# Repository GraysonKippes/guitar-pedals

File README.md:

# Guitar Pedals
A collection of custom guitar pedals designed and built by me.
## Fuzzy Mk. 1
[Main Article](fuzz_mk1/)

A simple fuzz pedal, this is my first guitar pedal.
It amplifies the input signal and limits the output signal, shaping it into a more blocky, thick waveform.
The circuit consists of an op-amp amplifier-limiter circuit, as well as a 2:1 analog mux and an electronic toggle latch for bypass functionality.
It runs on 9VDC, which is standard for guitar pedals.

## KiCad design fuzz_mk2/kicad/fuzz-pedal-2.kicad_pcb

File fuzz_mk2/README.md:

# Fuzzy Mk. 2
The Fuzzy Mk. 2 is an analog fuzz-style distortion pedal with two-band tone control.

## Circuit Overview
The effect path consists of two stages: the fuzz distortion, then the tone control.
The fuzz distortion is the main part of the circuit, and the tone control is an add-on inspired by the Big Muff Pi requested by my client.
I upcharged him (and every other buyer) for it.

### Fuzz Distortion
Fuzz distortion works by heavily amplifying a signal past the output range of the amplifier, resulting in a heavily clipped waveform that resembles a square wave.
Like the Mk. 1, I implement this clipping not with overdriving an amplifier, but with an op-amp limiter circuit.
This means I control the limit level in the signal feedback path, rather than by adjusting the voltage delivered to the op-amp's supply pins.
Op-amps often have assymetrical headroom under the positive rail and over the negative rail; i.e. output can get closer to the negative rail than to the positive rail.
This would result in an assymetrical clipping, which, while probably an interesting distortion effect, is not what I am going for.
(At any rate, I could implement assymetrical clipping in the signal feedback path if I wanted to.)

Also, controlling the limit level through the power rails would most likely amount to powering the op-amp through a voltage divider, and the op-amp itself would end up loading the voltage divider when it draws current, changing the divider ratio.
On top of that, using the power rails to control the signal in such a way would leak any ripple in the power supply into the signal, which is incredibly undesirable.

As a side note, I believe that one could implement "softer" distortions (such as overdrive) by increasing the resistances of the resistors in the limiter voltage divider, relative to the resistors in the amplifier voltage divider.
This would cause the limiter to "sag" and not clip the signal as hard.

### Tone Control
The tone control works by splitting the signal path into two paths: one that is fed into a low-pass filter, and one that is fed into a high-pass filter.
The two paths are then added back together.

More specifically, my tone control is essentially the Big Muff Pi (by Electro-Harmonix) tone control, with two crucial modifications.
1. The filters and the adder circuits were converted from one big passive network to three op-amp circuits, effectively buffering each stage.
2. The filters were designed to share the same cut-off frequency, rather than have two separate frequencies.

By converting the passive network into distinct active stages, they no longer sag each other down.
Also, by making the tone control stages active, I can further boost the signal if needed and buffer the output, not having a high impedance output.

The original Big Muff Pi pedal has a different cut-off frequency for each filter, with a lower cut-off for the low-pass filter and a higher cut-off for the high-pass filter.
When the two filtered paths are added back together, a gap is left behind in the frequency response.
This is the "mid-range scoop" for which this pedal is infamous; guitarists have agonized over how to compensate for this, when I simply restore that band of frequencies.

The adder stage of the tone control consists of nothing more than a potentiometer (which connects the outputs of the filters together) with the center tap buffered by an op-amp.
This allows the user to set a ratio with which the low-pass and high-pass lines are mixed.
For example, setting the pot wiper three-quarters along the way to the low-pass end means that the output will receive 75% low-pass and 25% high-pass.

My main goal with the tone control was to have it so that the frequency response would be totally flat when set to 50/50 mix; that is, the signal would sound the same, as though there was no tone control at all.
matching the cut-off frequencies of the filters ensures this, and this can be proven mathematically by adding the frequency responses of the two filters:

$$ \frac{1}{1 + sRC} + \frac{sRC}{1 + sRC} = \frac{1 + sRC}{1 + sRC} = 1 $$

This result is confirmed with an LTspice simulation of the tone control circuit.

## Component Selection

### Operational Amplifiers
In my opinion, the only components in this circuit worth discussing in depth are the op-amps; no need to discuss the resistors and capacitors.
I originally wanted to pick out nice op-amps from the Burr-Brown line, and I spent a lot of time sifting through the parts.
I settled on an OPA1641 for the buffer input and an OPA1679 for the signal processing.
However, by the time I got around to ordering the parts, the OPA1679 went out of stock.
(This has happened before too, with an STM32H7A3, which is why that project is on hiatus).
So I bought a TL074 instead, which is thankfully pin-compatible.

All the noiselessness of the newer op-amps is pretty much pointless anyways, given the fact that guitar pedal setups are riff with stray inductances and ground loops.
So for this reason (and a few others), I will probably just stick to the TL07x and NE5532 op-amps going forward.

I picked the OPA1641 because it is a JFET input and thus has much higher input impedance and can handle higher impedance sources.
According the Google, JFET inputs are supposed to have this rich, warm tone to them that guitarists like.
It's probably nonsense, but when in Rome, do as the Romans do.

I picked a quad op-amp package for the signal processing to fit it all into one neat package, but it ended up being more a hassle to route to be honest.
The main benefit I see of quad op-amps is that they seem to all or mostly use the same standard pin-out, whereas single- and dual- packages have different pin-outs.
I have read before that quad op-amps have all these issues, including increased crosstalk noise and higher power consumption; but to be honest, other than the more restricted routing, I doubt that these supposed issues are real, or if they are real, actually matter.
Again, the noise from patch cables and ground loop hums dominates whatever noise there is or isn't in the op-amps.

### Indicator LEDs
I selected a green LED for the power-on indicator and a blue LED for the effect-on indicator.
The consquence of this was that I needed two different current-limiting resistors to match their power levels.
For each LED, I calculate the resistance needed using Ohm's Law with the forward voltage and test current in the LED's datasheet:

$$ R_{LED} = \frac{V_{CC} - V_{F}}{I_{F}}$$

The calculated resistance value must be rounded to the nearest standard EIA value.

## Comparison to Fuzzy Mk. 1
In all honesty, the first fuzz pedal was completely overengineered with the analog mux and the 555 timer used as a bistable latch.
Getting rid of those massively simplified the circuit design and freed up room for other circuitry (namely the tone control).
At any rate, the 555-based toggle functionality was really buggy and just a nuisance overall.
Probably the biggest embarrassment in my opinion was using the 555 timer output to control a transistor switch that in turn controlled the mux, which was utterly pointless.

I still believe that an electronic switch (controlled by a mechanical switch) is superior to a purely mechanical switch for a few reasons.
1. Switch bouncing can be eliminated by placing a low-pass filter on the base/gate of the electronic switch.
2. The signal path does not have to be run all the way back to the footswitch (optimizing PCB trace length is pointless for noise, but it would make routing easier).
3. The switch could be controlled however I want, and I am not just limited to the mechanical switch functionality.
That being said, I would rather implement the electronic switching with discrete transistors than spend $6 on a single mux IC again, especially since switches are needed on both the input and output, doubling the cost.

Besides the core circuit design, I also introduced circuit protection to Fuzzy Mk. 2, which was not at all present in Mk. 1.
Fuzzy Mk. 2 includes reverse polarity protection and overvoltage protection on the power port, as well as ESD protection on both power port and audio jacks.
Reverse polarity protection is likely the most important form of protection for guitar pedals, since guitar pedals, for whatever reason, use a center-negative configuration with their power jacks.
This means that it is especially easy to accidentally reverse the polarity on the power, by plugging in a standard center-positive power plug. 

## Future Revisions
There are a few revisions I would like to implement for Fuzzy Mk. 3, should I ever build it.
 - Design the board such that it can fit in a standard metal stompbox, so that I don't have to have a custom 3D printed case.
 - Put the footswitch on the lower end of the board, underneath the potentiometers, so that the guitarist doesn't accidentally stomp on the pot knobs.
 - Implement electronic switches using discrete transistors, as described above.
 - Just use two dual-channel TL072s or NE5532s for the effect path (and a TL071 for the input buffer).
 - Include some stylish graphics on the board for the sake of posterity.

## Bill of Materials
A shortened bill of materials is presented below:
| Reference | Description | MPN | Quantity | Extended Price |
|-----------|-------------|-----|----------|----------------|
| C1-2 | CAP ALUM 1UF 20% 50V SMD | 865060640001 | 2 | $0.34 |
| C3, C7 | CAP CER 0.1UF 50V X7R 0805 | C0805C104K5RACTU | 2 | $0.36 |
| C4, C6 | CAP CER 2200PF 50V X7R 0805 | C0805C222K5RACTU | 2 | $0.20 |
| C5 | CAP ALUM 10UF 20% 35V SMD | 865080642006 | 1 | $0.20 |
| D1-2 | TVS DIODE 5.5VWM 14VC SOT5X3 | TPD1E10B06DYAR | 2 | $1.10 |
| D3 | TVS DIODE 10VWM 17VC DO214AC | SMAJ10A | 1 | $0.51 |
| D4 | DIODE SCHOTTKY 50V 1A DO214AC | SS15 | 1 | $0.76 |
| D5 | LED GREEN DIFFUSED 5MM ROUND T/H | 151051VS04000 | 1 | $0.25 |
| D6, D7 | DIODE STANDARD 75V 250MA SOD123 | 1N4148W | 2 | $0.28 |
| D8 | LED BLUE DIFFUSED 5MM ROUND T/H | 151051BS04000 | 1 | $0.25 |
| J1 | CONN PWR JACK 2X5.5MM KINKED PIN | PJ-202AH | 1 | $0.86 |
| J2-3 | JACK 1/4" MONO SWITCHED - FULL T | NMJ4HFD2 | 2 | $3.54 |
| R1-8 | RES 100K OHM 1% 1/8W 0805 | RMCF0805FT100K | 8 | $0.80 |
| R9, R11 | RES 51K OHM 1% 1/8W 0805 | RMCF0805FT51K0 | 2 | $0.20 |
| R10 | RES 360 OHM 1% 1/8W 0805 | RMCF0805FT360R | 1 | $0.10 |
| R12 | RES 300 OHM 1% 1/8W 0805 | RMCF0805FT300R | 1 | $0.10 |
| R13, R16 | RES 1K OHM 1% 1/8W 0805 | RMCF0805FT1K00 | 2 | $0.22 |
| R14-15 | RES 220 OHM 1% 1/8W 0805 | RMCF0805FT220R | 2 | $0.20 |
| RV1-2 | POT 1M OHM 0.08W CARBON LINEAR | PDB12-H4301-105BF | 2 | $3.00 |
| SW1* | Footswitch | N/A | 1 | N/A |
| U1 | IC OP AMP 1CH 8-SOIC | OPA1641AIDR | 1 | $2.56 |
| U2 | IC OP AMP 4CH 14-SOIC | OPA1679IDR | 1 | $1.72 |

*Purchased from a different vendor than DigiKey.

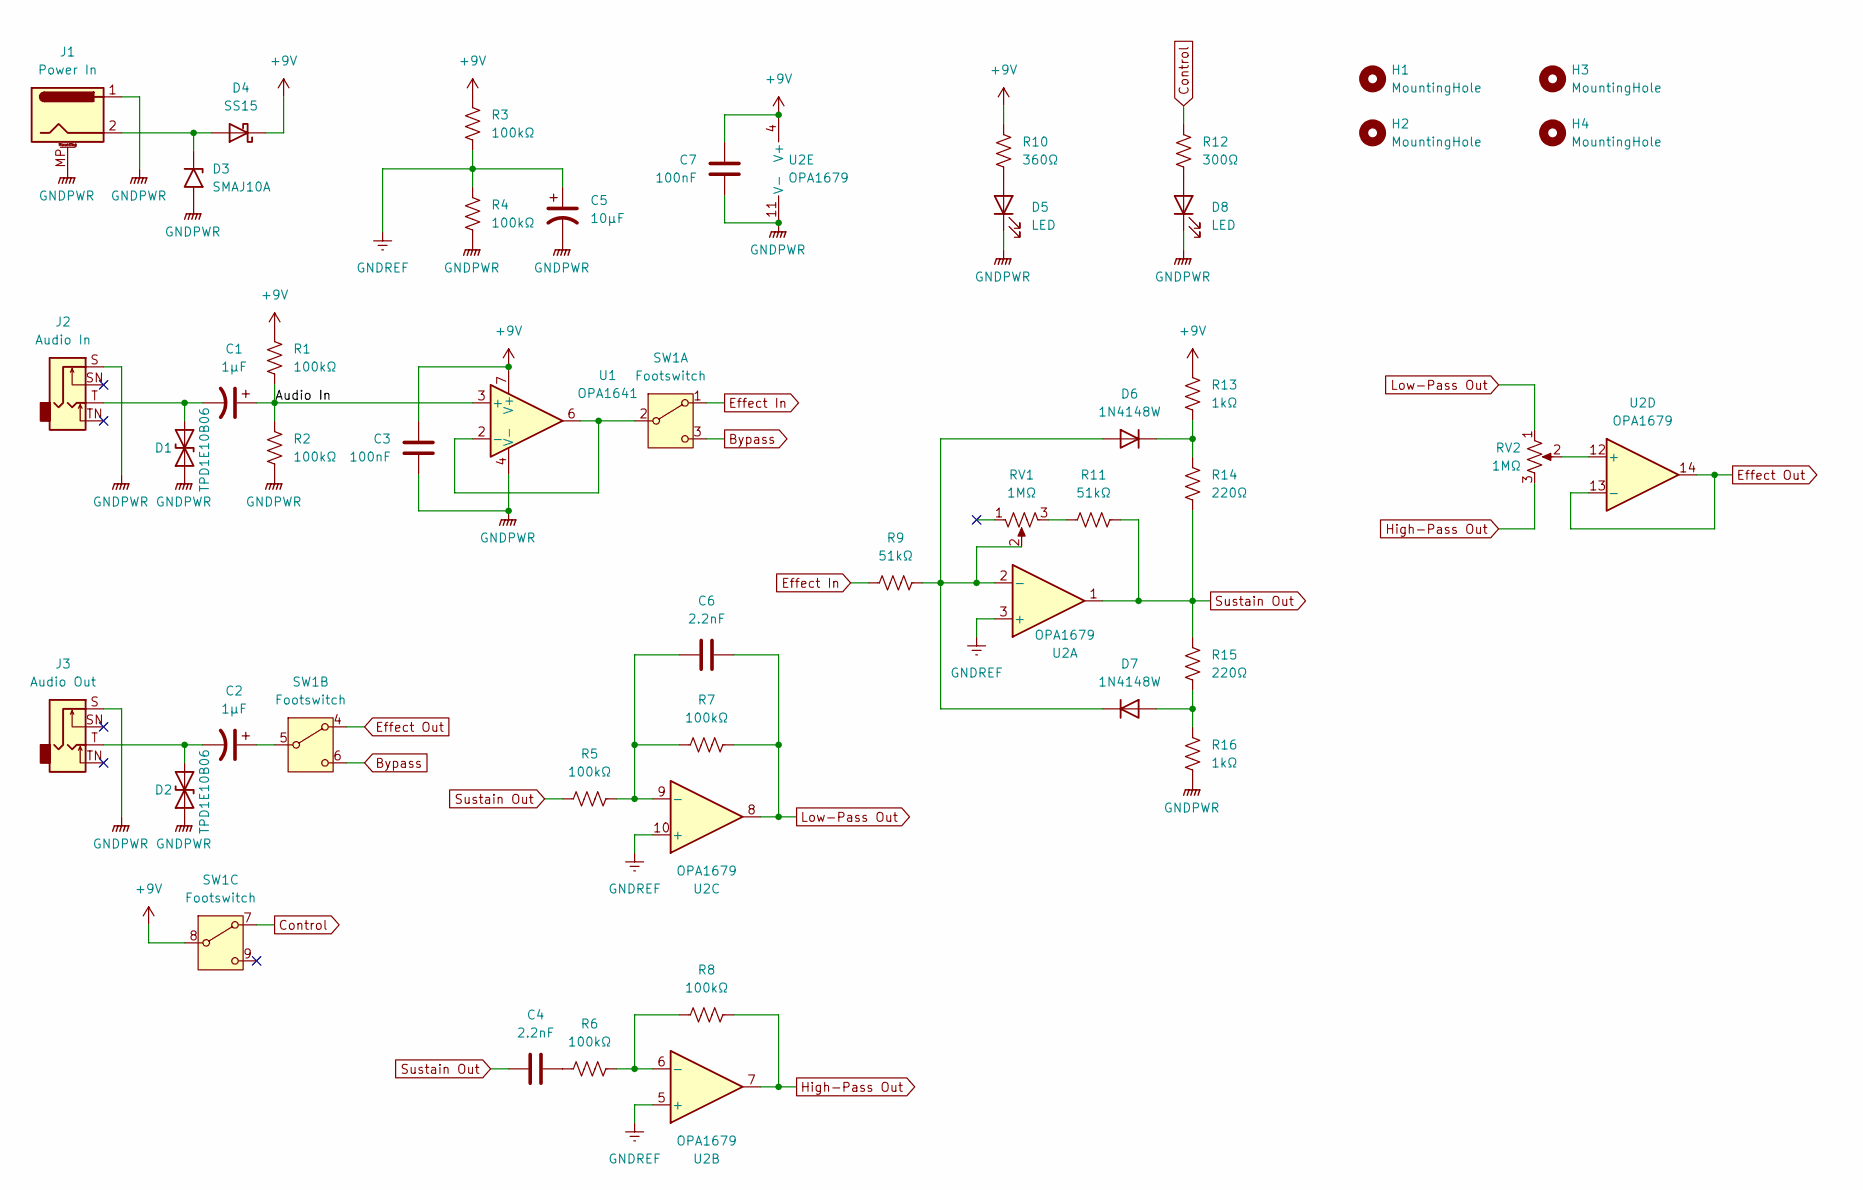
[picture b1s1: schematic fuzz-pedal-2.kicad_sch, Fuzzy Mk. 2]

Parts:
C1, C2: 1μF; CP_Elec_4x5.4
C3, C7: 100nF; C_0805_2012Metric_Pad1.18x1.45mm_HandSolder
C4, C6: 2.2nF; C_0805_2012Metric_Pad1.18x1.45mm_HandSolder
C5: 10μF; CP_Elec_5x5.4
D1, D2: TPD1E10B06; D_SOD-523
D3: SMAJ10A; D_SMA
D4: SS15; D_SMA_Handsoldering
D5, D8: LED; LED_D5.0mm
D6, D7: 1N4148W; D_SOD-123
H1, H2, H3, H4: MountingHole; MountingHole_2.2mm_M2
J1: Power In; CUI_PJ-202AH
J2: Audio In; Jack_6.35mm_Neutrik_NMJ4HFD2_Horizontal
J3: Audio Out; Jack_6.35mm_Neutrik_NMJ4HFD2_Horizontal
R1, R2, R3, R4, R5, R6, R7, R8: 100kΩ; R_0805_2012Metric_Pad1.20x1.40mm_HandSolder
R9, R11: 51kΩ; R_0805_2012Metric_Pad1.20x1.40mm_HandSolder
R10: 360Ω; R_0805_2012Metric_Pad1.20x1.40mm_HandSolder
R12: 300Ω; R_0805_2012Metric_Pad1.20x1.40mm_HandSolder
R13, R16: 1kΩ; R_0805_2012Metric_Pad1.20x1.40mm_HandSolder
R14, R15: 220Ω; R_0805_2012Metric_Pad1.20x1.40mm_HandSolder
RV1, RV2: 1MΩ; POT_PDB12-H_301_BRN
SW1: Footswitch; Switch_3PDT
U1: OPA1641; SOIC-8_3.9x4.9mm_P1.27mm
U2: OPA1679; SOIC-14_3.9x8.7mm_P1.27mm

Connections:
+9V: C3.1, C7.1, D4.1 (K), R1.2, R3.1, R10.2, R13.2, SW1.8, U1.7 (V+), U2.4 (V+)
/Audio In: C1.1, R1.1, R2.2, U1.3 (+)
Bypass: SW1.3, SW1.6
Control: R12.2, SW1.7
Effect In: R9.1, SW1.1
Effect Out: SW1.4, U2.13 (-), U2.14
GNDPWR: C3.2, C5.2, C7.2, D1.1 (A1), D2.1 (A1), D3.2 (A2), D5.1 (K), D8.1 (K), J1.1, J1.MP (MountPin_MP), J2.S, J3.S, R2.1, R4.2, R16.1, U1.4 (V-), U2.11 (V-)
GNDREF: C5.1, R3.2, R4.1, U2.3 (+), U2.5 (+), U2.10 (+)
High-Pass Out: R8.2, RV2.3, U2.7
Low-Pass Out: C6.1, R7.2, RV2.1, U2.8
unnamed: C2.1, SW1.5
unnamed: C4.1, R6.1
unnamed: C1.2, D1.2 (A2), J2.T
unnamed: C2.2, D2.2 (A2), J3.T
unnamed: D3.1 (A1), D4.2 (A), J1.2
unnamed: D5.2 (A), R10.1
unnamed: D6.2 (A), D7.1 (K), R9.2, RV1.2, U2.2 (-)
unnamed: D6.1 (K), R13.1, R14.2
unnamed: D7.2 (A), R15.1, R16.2
unnamed: D8.2 (A), R12.1
unnamed: R11.1, RV1.3
unnamed: SW1.2, U1.2 (-), U1.6
unnamed: R6.2, R8.1, U2.6 (-)
unnamed: C6.2, R5.2, R7.1, U2.9 (-)
unnamed: RV2.2, U2.12 (+)
Sustain Out: C4.2, R5.1, R11.2, R14.1, R15.2, U2.1

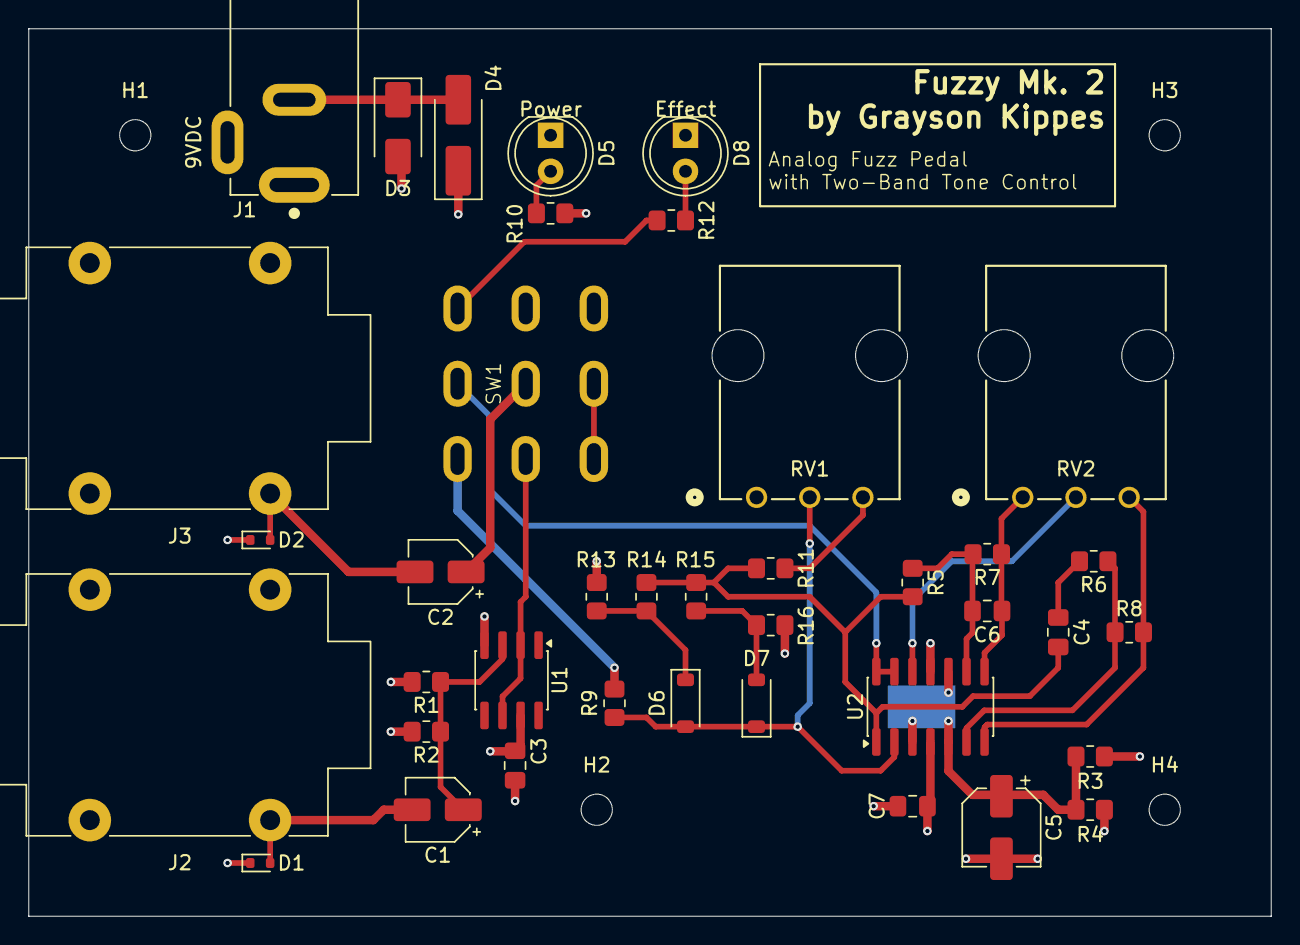
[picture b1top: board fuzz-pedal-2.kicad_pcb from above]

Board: 4 copper layers, 87.5 x 62.5 mm, 43 parts (0 on the bottom side), 26 nets.

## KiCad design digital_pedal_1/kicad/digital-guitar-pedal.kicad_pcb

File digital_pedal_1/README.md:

# Digital Guitar Pedal

This is an ongoing project for a digital signal processing system for electric guitars.
It provides multiple effects which can be individually adjusted using four knobs.

## Motivation

I had seen several job postings from certain large engineering firms that included "ARM Cortex" among the qualifications and preferred skills;
I decided that having that technology on my resume would be great for my career prospects.
Moreover, signal processing, particularly digital signal processing, is really interesting to me,
so I wanted to build a digital signal processing system that used an ARM processor.

## Goals

##### Low Noise and Distortion
Electric guitar pedal enthusiasts tend to hold digital audio processing technology in suspicion, preferring the supposed purity of analog technology.
Therefore, my first goal was to minimize noise and distortion.

##### Low Power Consumption
Guitarists also like to chain several pedals together, but the power supply can only supply enough power for so many pedals at once;
the more power a particular pedal draws, the fewer other pedals the guitarist can add to the chain.
Digital pedals tend to consume more power than analog pedals, so minimizing the power draw of this pedal is a much larger concern of mine compared to the analog pedals I have designed.

## Hardware Overview

### Parts Selection

#### STM32H7A3

The STM32H7A3 is from STMicroelectronics H7-series of high-performance microcontrollers.
I was originally considering the older F4-series and G4-series, 
but I decided that if I am going through the effort of developing the hardware for a DSP system, 
I should just get a much nicer and more modern controller, so that I would never be bottlenecked by the hardware.

The STM32H7A3 is an ARM Cortex-M7 processor, which, as stated above, is a technology I wanted to put on my resume.
In addition to this, STM32 microcontrollers in general are very popular among hobbyists, so there should be a lot of documentation and tutorials available online.

#### PCM3060

The PCM3060 is a hardware codec (meaning it incorporates an ADC and a DAC in one chip) from Texas Instruments.
The built-in ADC and DAC on the STM32H7A3 are 12-bits and 10-bits, respectively, meaning they did not have high enough resolution to be used for audio signal processing.
Like the STM32H7A3, the PCM3060 is popular among hobbyists, so there should be plenty of documentation online.

### Power Scheme

The power scheme of the hardware is of the utmost importance to both of my stated goals with this project.
It wouldn't matter if I could procure ideal amplifiers with no noise whatsoever, if the power rails themselves were noisy.
I decided to combine both switching regulators and LDO regulators to reap the benefits of both.
The only downsides of this approach would be the increased component count and additional board complexity/space;
but since I put a 144-pin chip on this board, a couple extra small chips didn't bother me.

The power scheme includes two main power rails: the digital 3.3V rail and the analog 5V rail.
The digital rail supplies both the STM32H7A3 and the PCM3060 digital VDD;
the analog rail supplies the PCM3060 analog VCC and the input/output op-amp buffers.
The digital rail is created with only a single switching regulator (AP5100) bucking the 9V input directly down to 3.3V.
The analog rail is created with a switching regulator (AP5100) bucking the 9V down to approximately 5.9V, and a LDO regulator (MCP1754) shifting it down to a very clean 5V.

In addition to the power rails, I configured the STM32H7A3 to bypass the internal LDO, only using the internal SMPS to supply its core voltage, thus reducing the microcontroller's power consumption considerably.
I also cut out the analog supply to the STM32H7A3.
I was able to do both these things because I offloaded all analog functions to the PCM3060, thus eliminating the need for a really clean power supply to the STM32H7A3.

### User Interface

The board includes a footswitch, four rotary encoders, and a small character-only display.
The footswitch enables/disables then entire effect; if pressed down, the audio signal bypasses the entire codec and microcontroller, instead being routed through a single op-amp buffer.
The four rotary encoders act as generic knobs which control different parameters for each effect.
The display shows the current effect and current parameter being adjusted.

## Software Overview

Coming soon.

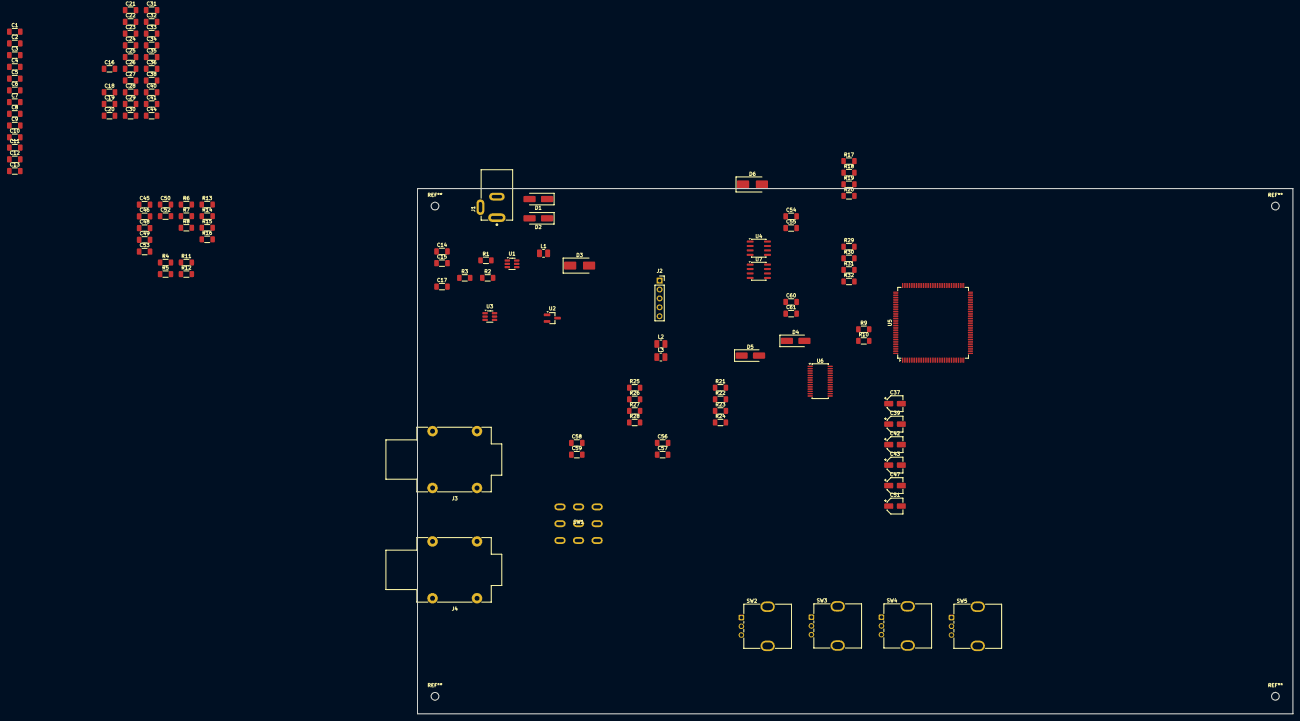
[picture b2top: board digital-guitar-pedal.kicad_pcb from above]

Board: 4 copper layers, 250.0 x 150.0 mm, 118 parts (0 on the bottom side), 61 nets, no tracks yet.

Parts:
C1, C2, C3, C4, C5, C6, C7, C8, C9, C10, C11, C12, C18, C20, C21, C22, C23, C36, C38, C40, C45, C46, C48, C49, C53: 100nF; C_1206_3216Metric_Pad1.33x1.80mm_HandSolder
C13, C25, C33, C34: 4.7μF; C_1206_3216Metric_Pad1.33x1.80mm_HandSolder
C14, C29: 22nF; C_1206_3216Metric_Pad1.33x1.80mm_HandSolder
C15, C30: 100pF; C_1206_3216Metric_Pad1.33x1.80mm_HandSolder
C16, C31: 22μF; C_1206_3216Metric_Pad1.33x1.80mm_HandSolder
C17, C26, C32: 10μF; C_1206_3216Metric_Pad1.33x1.80mm_HandSolder
C19, C24, C27, C28: 1μF; C_1206_3216Metric_Pad1.33x1.80mm_HandSolder
C35: 220pF; C_1206_3216Metric_Pad1.33x1.80mm_HandSolder
C37, C39, C43, C47: 10μF; CP_Elec_4x5.4
C41: 470pF; C_1206_3216Metric_Pad1.33x1.80mm_HandSolder
C42, C51: 4.7μF; CP_Elec_4x5.4
C44: 3300pF; C_1206_3216Metric_Pad1.33x1.80mm_HandSolder
C50, C52: 100pF; R_1206_3216Metric_Pad1.30x1.75mm_HandSolder
C54, C55, C56, C57, C58, C59, C60, C61: 10nF; C_1206_3216Metric_Pad1.33x1.80mm_HandSolder
D1: SS15; D_SMA_Handsoldering
D2: SMAJ20A; D_SMA_Handsoldering
D3, D6: B230; D_SMB_Handsoldering
D4, D5: SMAJ6.0CA; D_SMA_Handsoldering
J1: Power In; CUI_PJ-202AH
J2: ST-LINK; PinSocket_1x05_P2.54mm_Vertical
J3: Audio In; Jack_6.35mm_Neutrik_NMJ4HFD2_Horizontal
J4: Audio Out; Jack_6.35mm_Neutrik_NMJ4HFD2_Horizontal
L1, L2, L3: 2.2μH; L_1008_2520Metric_Pad1.43x2.20mm_HandSolder
R1, R6: 100kΩ; R_1206_3216Metric_Pad1.30x1.75mm_HandSolder
R2: 49.9kΩ; R_1206_3216Metric_Pad1.30x1.75mm_HandSolder
R3: 16.2kΩ; R_1206_3216Metric_Pad1.30x1.75mm_HandSolder
R4: 47Ω; R_1206_3216Metric_Pad1.30x1.75mm_HandSolder
R5, R12, R17, R18, R19, R20, R21, R22, R23, R24, R25, R26, R27, R28, R29, R30, R31, R32: 10kΩ; R_1206_3216Metric_Pad1.30x1.75mm_HandSolder
R7, R14, R15: 75kΩ; R_1206_3216Metric_Pad1.30x1.75mm_HandSolder
R8: 12kΩ; R_1206_3216Metric_Pad1.30x1.75mm_HandSolder
R9, R10: 4.7kΩ; R_1206_3216Metric_Pad1.30x1.75mm_HandSolder
R11: 7.5kΩ; R_1206_3216Metric_Pad1.30x1.75mm_HandSolder
R13: 750Ω; R_1206_3216Metric_Pad1.30x1.75mm_HandSolder
R16: 1MΩ; R_1206_3216Metric_Pad1.30x1.75mm_HandSolder
SW1: Foot Switch; Switch_3PDT
SW2, SW3, SW4, SW5: Encoder; RotaryEncoder_Bourns_Vertical_PEC12R-3x17F-Nxxxx
U1, U3: AP5100; SOT-23-6_Handsoldering
U2: MCP1754S-5002xCB; SOT-23_Handsoldering
U4, U7: OPA2156xD; SOIC-8_3.9x4.9mm_P1.27mm
U5: STM32H7A3ZITxQ; LQFP-144_20x20mm_P0.5mm
U6: PCM3060; TSSOP-28_4.4x9.7mm_P0.65mm

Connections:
+3.3V: C1.1, C2.1, C3.1, C4.1, C5.1, C6.1, C7.1, C8.1, C9.1, C10.1, C11.1, C12.1, C13.1, C15.1, C16.1, C18.1, C19.1, C20.1, C21.1, C22.1, C23.1, C24.1, C25.1, C26.1, C36.1, C37.1, J2.1, L1.2, R2.1, R4.2, R9.1, R10.1, R17.2, R18.2, R21.2, R22.2, R25.2, R26.2, R29.2, R30.2, U5.7 (VDD), U5.8 (VBAT), U5.13 (VDD), U5.16 (VDDSMPS), U5.19 (VDD), U5.32 (VDD), U5.42 (VDD), U5.56 (VDD), U5.70 (VDDLDO), U5.71 (VDD), U5.79 (VDD), U5.90 (VDD50_USB), U5.91 (VDD33_USB), U5.92 (VDD), U5.105 (VDDLDO), U5.106 (VDD), U5.119 (VDDMMC), U5.129 (VDD), U5.142 (PDR_ON), U5.143 (VDDLDO), U5.144 (VDD), U6.7 (V_{DD})
+5VA: C28.1, C38.1, C39.1, C40.1, C53.1, U2.2 (VO), U4.8 (V+), U6.24 (V_{CC}), U7.8 (V+)
+9V: C17.1, C32.1, D1.1 (K), D2.1 (A1), R1.2, R6.2, U1.5 (IN), U3.5 (IN)
/Encoder A/A: C54.1, R19.1
/Encoder A/B: C55.1, R20.1
/Encoder B/A: C56.1, R23.1
/Encoder B/B: C57.1, R24.1
/Encoder C/A: C58.1, R27.1
/Encoder C/B: C59.1, R28.1
/Encoder D/A: C60.1, R31.1
/Encoder D/B: C61.1, R32.1
Audio In: D4.2 (A2), J3.T, SW1.2
Audio Out: D5.2 (A2), J4.T, SW1.5
Bypass In: SW1.3, U7.5 (+)
Bypass Out: SW1.6, U7.6 (-), U7.7
Effect In: R14.1, R16.2, SW1.1
Effect Out: C43.2, SW1.4
GNDA: C1.2, C2.2, C3.2, C4.2, C5.2, C6.2, C7.2, C8.2, C9.2, C10.2, C11.2, C12.2, C13.2, C16.2, C17.2, C18.2, C19.2, C20.2, C21.2, C22.2, C23.2, C24.2, C25.2, C26.2, C27.2, C28.2, C31.2, C32.2, C33.2, C34.2, C35.2, C36.2, C37.2, C38.2, C39.2, C40.2, C42.2, C44.1, C45.2, C46.2, C47.2, C48.2, C49.2, C52.2, C53.2, C54.2, C55.2, C56.2, C57.2, C58.2, C59.2, C60.2, C61.2, D2.2 (A2), D3.2 (A), D4.1 (A1), D5.1 (A1), D6.2 (A), J1.1, J1.MP (MountPin_MP), J2.2, J3.S, J4.S, R3.2, R5.1, R8.2, SW2.C, SW3.C, SW4.C, SW5.C, U1.2 (GND), U2.1 (GND), U3.2 (GND), U4.4 (V-), U4.5 (+), U5.6 (VSS), U5.12 (VSS), U5.14 (VSSSMPS), U5.18 (VSS), U5.33 (VSS), U5.34 (VSSA), U5.36 (VDDA), U5.41 (VSS), U5.55 (VSS), U5.69 (VSS), U5.80 (VSS), U5.89 (VSS), U5.104 (VSS), U5.118 (VSS), U5.128 (VSS), U5.141 (VSS), U6.8 (DGND), U6.16 (SGND), U6.22 (AGND2), U6.23 (AGND1), U7.4 (V-)
I2C.SCL: R9.2, U5.133 (PB6), U6.1 (MC/SCL/FMT)
I2C.SDA: R10.2, U5.134 (PB7), U6.2 (MD/SDA/DEMP)
I2S.BCK: U5.4 (PE5), U6.5 (BCK1), U6.10 (BCK2)
I2S.MCK: U5.1 (PE2), U6.6 (SCKI1), U6.9 (SCKI2)
I2S.SD_A: U5.5 (PE6), U6.3 (DOUT)
I2S.SD_B: U5.2 (PE3), U6.12 (DIN)
I2S.WS: U5.3 (PE4), U6.4 (LRCK1), U6.11 (LRCK2)
NRST: J2.5, U5.27 (NRST)
unnamed: C41.2, C43.1, R11.2, U4.1
unnamed: C44.2, R11.1, R12.2, R13.1
unnamed: C50.1, R14.2, R15.1
unnamed: D1.2 (A), J1.2
unnamed: C14.2, D3.1 (K), L1.1, U1.6 (SW)
unnamed: C29.2, D6.1 (K), L2.1, U3.6 (SW)
unnamed: R17.1, R19.2, SW2.A
unnamed: R18.1, R20.2, SW2.B
unnamed: R21.1, R23.2, SW3.A
unnamed: R22.1, R24.2, SW3.B
unnamed: R25.1, R27.2, SW4.A
unnamed: R26.1, R28.2, SW4.B
unnamed: R29.1, R31.2, SW5.A
unnamed: R30.1, R32.2, SW5.B
unnamed: C14.1, U1.1 (BST)
unnamed: R1.1, U1.4 (EN)
unnamed: C15.2, R2.2, R3.1, U1.3 (FB)
unnamed: C27.1, C30.1, C31.1, L2.2, R7.1, U2.3 (VI)
unnamed: C29.1, U3.1 (BST)
unnamed: R6.1, U3.4 (EN)
unnamed: C30.2, R7.2, R8.1, U3.3 (FB)
unnamed: C41.1, R13.2, U4.3 (+)
unnamed: U4.6 (-), U4.7
unnamed: R5.2, U5.135 (BOOT0)
unnamed: C33.1, C34.1, C48.1, C49.1, L3.1, U5.17 (VFBSMPS), U5.68 (VCAP), U5.103 (VCAP), U5.140 (VCAP)
unnamed: C35.1, L3.2, U5.15 (VLXSMPS)
unnamed: R4.1, U5.35 (VREF+)
unnamed: C42.1, U6.26 (V_{IN}R)
unnamed: C52.1, R15.2, U7.3 (+)
unnamed: C50.2, C51.2, U7.1, U7.2 (-)
PCM3060.VCOM: C45.1, C46.1, C47.1, R16.1, U4.2 (-), U6.21 (V_{COM})
PCM3060.V_{IN}L: C51.1, U6.25 (V_{IN}L)
PCM3060.V_{OUT}L+: R12.1, U6.20 (V_{OUT}L+)
SWCLK: J2.4, U5.107 (PA14)
SWDIO: J2.3, U5.102 (PA13)

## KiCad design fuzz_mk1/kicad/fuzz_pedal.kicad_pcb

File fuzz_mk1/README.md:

# Fuzzy Mk. 1
## Introduction
A fuzz pedal is a guitar pedal that distorts a signal by amplifying it and limiting it, cutting off the peaks and shaping the signal into something like a sqaure wave.
The Fuzzy Mk. 1, as my debut on the scene of DIY guitar pedals, is a simple fuzz pedal.
It offers a basic fuzzing effect and a buffered bypass controlled by a toggle switch.
The intensity of the fuzzing can be controlled (down to being outright disabled) by a knob.

## Circuit Operation
### Core Effect
The core fuzzing effect is implemented with a single op-amp circuit, which combines inverting amplification with limiting.

While I could have implemented the clipping by simply amplifying the signal past the supply voltages, there are a few issues with this.
For one, this would leave the signal at or near the supply voltages, which means it would need to be attenuated before passing it to the next pedal in the effect chain.
This would necessitate a second amplifier stage, so I would either have to give up the buffered bypass, or include a second op-amp on the board, which would increase costs.
Not only that, but variably attenuating a signal back to its original amplitude is a design challenge I did not want to have to solve.
Another issue is that some op-amps have different capabilities between the two supply rails: they can clip to the negative closer than they can clip to the positive.
This would result in an uneven clipping.
But most of all, I consider it poor design practice to deliberately exploit maximum ratings to achieve an effect.

The inverting amplification is implemented with two fixed resistors (R4, R5) and a potentiometer (RV1).
The maximum gain is -11 V/V, and by including R5 in series with the potentiometer, the minimum gain is -1 V/V (instead of 0).
The amplified signal is clipped at 3V and 6V, resulting in a maximum peak-to-peak amplitude of 3V.
This is one-third of the supply voltage of 9V, allowing for considerable headroom without overly attenuating the signal.
### Bypass Toggle
Most guitar pedals include a switch to toggle bypassing the effect, which means that the signal is passed directly to the next pedal in the chain.
In the Fuzzy Mk. 1, this toggle functionality is implemented with an analog 2:1 multiplexer, an electronic toggle latch, and a momentary pushbutton.
1. The momentary pushbutton, the only moving component on the board, acts as the user interface. It is only active as long as it is held down.
2. The electronic toggle latch, implemented with a 555 timer in bistable operation, converts the momentary activation to toggle activation.
3. The output of the toggle latch controls a low-side switch, implemented with a single NPN transistor, which pulls down the multiplexer's control pin.
4. The ADG419 2:1 analog multiplexer routes one of the two different signals to the output.

The electronic switching scheme was chosen over a purely mechanical scheme for a variety of reasons:
- Electronic switches feature much higher durability, as they do not undergo the stress that mechanical switches do.
- The critical signal path can be routed through a chip that can be placed anywhere on the board, unlike the mechanical switch.
- The electronic switch is programmable, providing flexibility in how it is activated. This is how I was able to convert momentary activation into toggle, saving costs on the switch.
- The main upside of mechanical switches--ability to handle larger loads--is not relevant, since this is not a power amplifier.
## Component Selection
For my first pedal, I elected to stick with simple through-hole components, including an op-amp for the core functionality of the pedal.
### NE5532 Operational Amplifier
The NE5532 op-amp is a classic op-amp that has been popular with audio enthusiasts for a few reasons.
#### Gain-Bandwidth Product
For one, TI's rendition of the NE5532 boasts a gain-bandwidth product of 12MHz.
In order for an amplifier to be useful for boosting audio signals, it needs to be able to handle the whole range of human hearing, which is about 20Hz to 20kHz.
By dividing the gain-bandwidth product by the upper end of human hearing, you get the maximum useful gain of an op-amp for audio signals.
In the case of the NE5532, you get a maximum useful gain of 600 V/V, or about 55.6dB.
In comparison, the antique LM741 has a gain-bandwidth product of 1.5MHz, which means it can only boost audio signals up to a gain of 75 V/V, or about 37.5dB.
#### Slew Rate
Another important feature of the NE5532 is a slew rate of 9 V/μS (or 5 V/μS for Texas Instruments' version).
The slew rate of an op-amp is the rate at which the voltage on its output pin can change.
In order for an amplifier to be useful for boosting audio signals, it needs to be able to slew fast enough to keep up with the signal.

To find out if the amplifier can do so, take the derivative of a sine (or cosine) wave at 20kHz with the desired peak-to-peak amplitude (actual voltage level, not gain), and find the derivative's maximum.
We only need to check the highest frequency because if the amplifier can slew fast enough for the highest frequency, it can slew fast enough for lower frequencies.
For example, imagine an amplifier that must produce a 10V peak-to-peak signal:
1. Represent the highest frequency with the equation $y(t) = 20sin(20000 \times 2\pi \times t)$.
2. Differentiate y(t): $y'(t) = 20cos(20000 \times 2\pi \times t) \times 20000 \times 2\pi$, via the Chain Rule.
3. Find the maximum of the derivative. The maximum of both sine and cosine, regardless of the parameter, is 1; so the maximum of the derivative is the constant coefficient.
4. Adjust the value to V/μS, by dividing it by 10^6. In this case, we get 2.51 V/μS. This value must be less than or equal to the slew rate of the op-amp.

For the fuzz pedal, or any standard guitar pedal, the single supply voltage--thus the maximum peak-to-peak amplitude--is 9V.
Therefore, the necessary slew rate is 1.13 V/μS, well under the maximum slew rate of the NE5532.
In comparison, the slew rate of the LM741 is 0.5 V/μS, which is not enough to amplify the whole human hearing range up to 9V peak-to-peak.

By the way, I believe that the slew rate is the reason why the limited peaks are not perfectly squared off but somewhat rounded, as seen in the LTspice simulation.
### ADG419 Analog Multiplexer
There's not much to say about the component itself.
I only selected it because it was what Digikey had for 2:1 analog multiplexers in a through-hole package.
The fact that it is a product of Analog Devices, meaning it was already in LTspice's standard part library, is an added bonus.
### NE555 Timer
The 555 timer, as it is colloquially referred to, is a versatile IC that is most commonly used for analog timing applications.
In this circuit, the timer runs in bistable operation, which means that it has two stable states: on and off.
More specifically, the timer operates as a toggle latch, so that the momentary pushbutton becomes a toggle pushbutton.
This toggle functionality could have been implemented in a variety of ways, but the 555 timer minimizes the number of components needed to do so.
Moreover, it is a very common part and easily replaced.
This let me order TI's NE555 in bulk so that I can use it in future projects, thus cutting down on costs.
### Small Components
The small components consist of a few common resistors and capacitors, as well as a couple diodes and a single discrete transistor.
For the resistors, I used what I had lying around, because whatever came in my Arduino kit is probably common and cheap enough to easily supply and replace.
These consist of blue metal-film resistors, which while being harder to read, are better because they lack the inductance of wire-wound resistors.
Most of the capacitors are ceramic, because they are not polarized and generally offer better characteristics; anything 10μF or above are aluminum electrolytic, mainly for bypass.

The diodes are 1N4148 diodes.
Unlike the resistors, I did not use what I had lying around, because what I have are 1N4007 diodes, which are for rectification and not for signal processing.
Conversely, 1N4148 diodes are better suited for signal processing, with faster switching and a lower forward voltage.
On the other hand, 1N4148 diodes are similarly cheap, cutting down on costs.

There is a single discrete transistor in the circuit, acting as a low-side switch for the ADG419 control pin.
When brought into saturation, it brings the control pin of the ADG419 down to ground, switching the output from the buffer to the fuzzer.
The schematic shows a 2N3904 transistor, which is a commonplace NPN BJT, because it's what KiCAD had in its standard parts library.
However, I ended up just soldering one of my 2N2222 transistors into the board, because that's what I had on hand, and both could work easily.
Really, any low-power NPN or NMOS transistor could work, though for MOS, the base/gate resistor (R11) is rendered unnecessary, because the MOSFET gate terminal draws virtually no current.
But again, 2N2222 is what I have on hand, and using a BJT and a resistor I already own is cheaper than buying a MOSFET.

The board also includes a 1MΩ potentiometer, for controlling the intensity of the fuzzing effect.
Realistically I could have used a 100kΩ or even a 10kΩ pot, but the large resistance value is a vestige from when the DC bias was on the signal input and not the noninverting op-amp input.
In that case, I had to ensure the voltage divider providing the DC bias was stiff compared to the feedback network, so the feedback resistors (including the pot) had to be relatively large.
## Simulations
This repository includes two LTspice simulations: one for the fuzzing effect and switching the output, one for the 555-driven toggle latch.
Not being able to afford laboratory equipment, this was the next best thing.
LTspice even came with ADG419 as part of its standard library of parts, since both LTspice and ADG419 are made by Analog Devices.
## Design Challenges
There were a few challenges involved with the design of this pedal:
 - Guitar pedals use a single supply rail (9VDC) instead of split supplies, meaning the input had to be DC biased.
 - Guitar pedal design standards have unusual quirks, which I had to keep in mind, such as the negative-center configuration of the power jacks.
 - User-facing components (buttons, knobs, connectors) dominated the layout, which was especially critical when the signal is routed through the component (i.e. through the potentiometer). I overcame this challenge by placing these components first and then placing the electronics around them.
 - I committed to a two-layer board layout with through-hole components and a ground plane, making routing tricky in some places. I overcame this challenge by placing ICs and their bypass capacitors close to each other, leaving room for passives between them, and then laying out the rest of the circuitry around them.
## Future Revisions
There are several improvements I can make for future revisions of this project:
 - Update some older components, such as replacing the NE5532 with TI's TLV9362 op-amp.
 - Use surface-mount devices instead of through-hole devices, thereby saving board space and reducing costs.
 - Replace the ADG419 with a less expensive alternative, as it is the most costly electronic component on the board.
 - Implement safety features, such as overcurrent protection and transient voltage suppression.
## References
- https://www.allaboutcircuits.com/technical-articles/an-op-amp-limiter-how-to-limit-the-amplitude-of-amplified-signals/ For the op-amp limiter design.
- https://youtu.be/dhzswWLUoG0?si=y4rR1ria-jn_BZjD For the 555 toggle latch design.

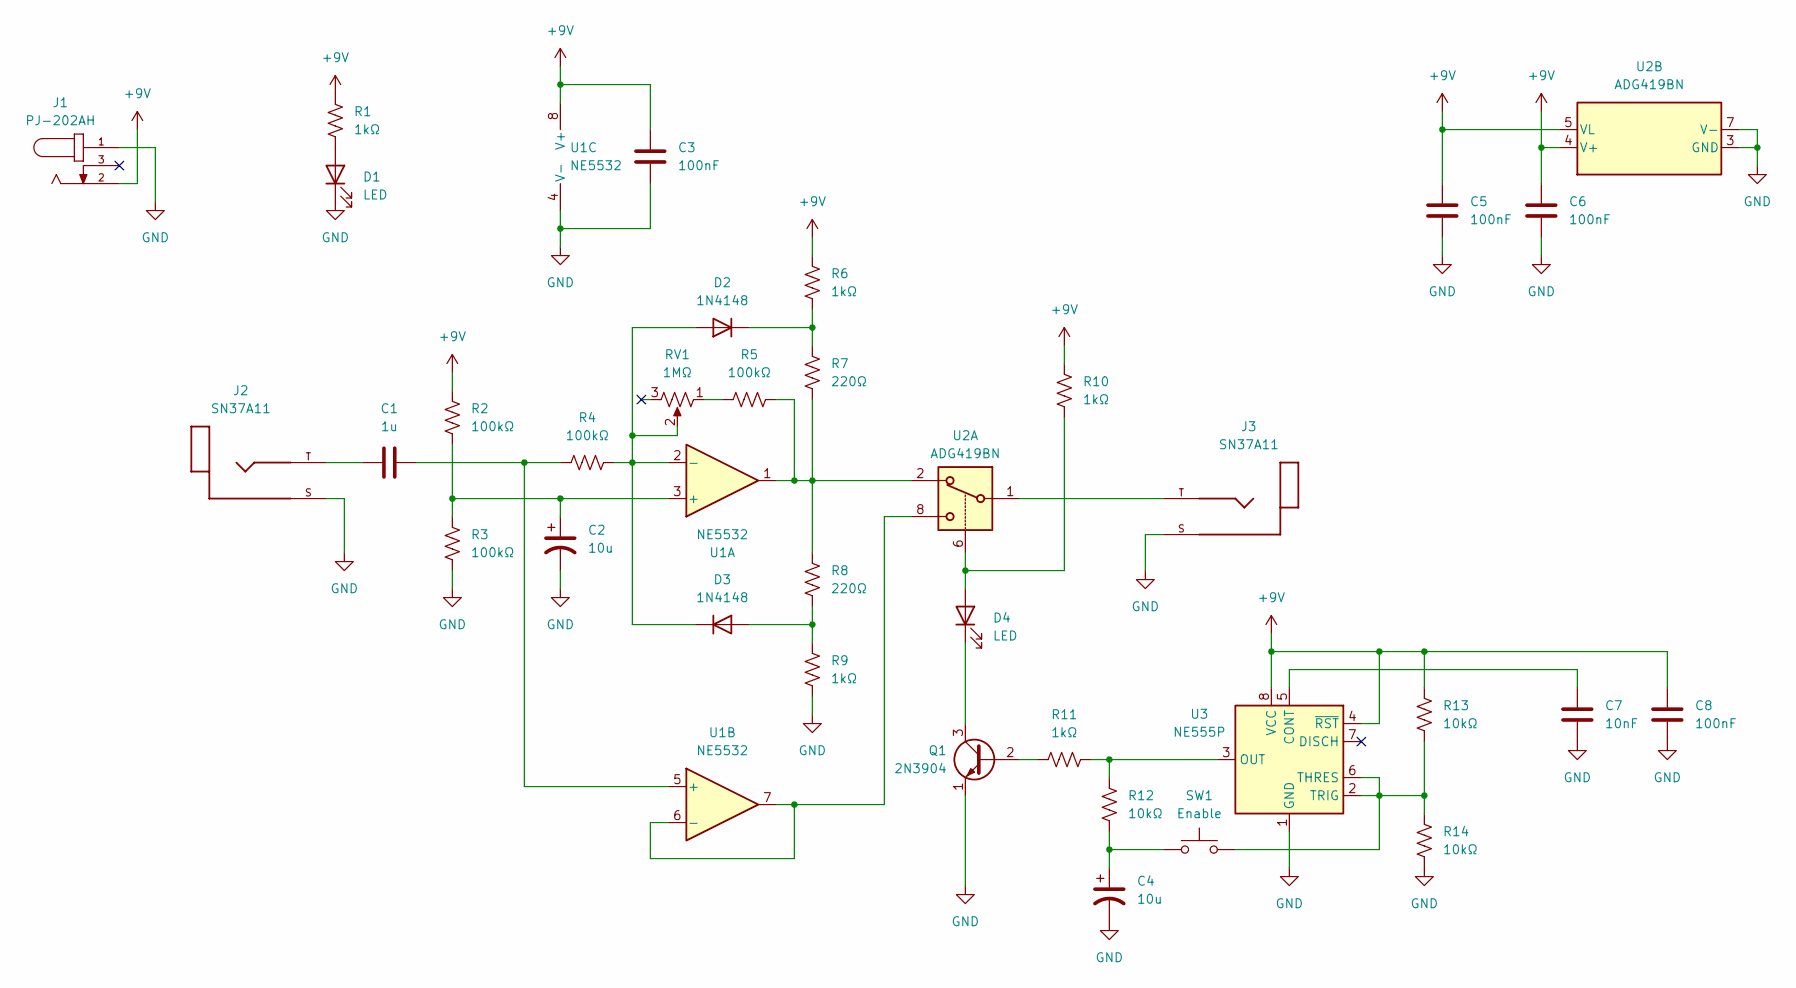
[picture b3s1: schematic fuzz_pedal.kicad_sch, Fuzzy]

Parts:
C1: 1u; C_Disc_D4.3mm_W1.9mm_P5.00mm
C2, C4: 10u; CP_Radial_D5.0mm_P2.50mm
C3, C5, C6, C8: 100nF; CAP_C320C_MR_X7R_KEM
C7: 10nF; CAP_C320C_MR_X7R_KEM
D1, D4: LED; LED_D3.0mm
D2, D3: 1N4148; D_DO-35_SOD27_P7.62mm_Horizontal
J1: PJ-202AH; CUI_PJ-202AH; PART_REV 1.02
J2, J3: SN37A11; SWITCHCRAFT_SN37A11; PARTREV F
Q1: 2N3904; TO-92_Inline
R1, R6, R9, R10, R11: 1kΩ; R_Axial_DIN0207_L6.3mm_D2.5mm_P7.62mm_Horizontal
R2, R3, R4, R5: 100kΩ; R_Axial_DIN0207_L6.3mm_D2.5mm_P7.62mm_Horizontal
R7, R8: 220Ω; R_Axial_DIN0207_L6.3mm_D2.5mm_P7.62mm_Horizontal
R12, R13, R14: 10kΩ; R_Axial_DIN0207_L6.3mm_D2.5mm_P7.62mm_Horizontal
RV1: 1MΩ; POT_PDB12-H_301_BRN
SW1: Enable; SW_NCE2
U1: NE5532; DIP-8_W7.62mm
U2: ADG419BN; DIP-8_W7.62mm
U3: NE555P; DIP-8_W7.62mm

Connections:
+9V: C3.1, C5.1, C6.1, C8.1, J1.2, R1.1, R2.1, R6.1, R10.1, R13.1, U1.8 (V+), U2.4 (V+), U2.5 (VL), U3.4 (~RST), U3.8 (VCC)
GND: C2.2, C3.2, C4.2, C5.2, C6.2, C7.2, C8.2, D1.1 (K), J1.1, J2.S, J3.S, Q1.1 (E), R3.2, R9.2, R14.2, U1.4 (V-), U2.3 (GND), U2.7 (V-), U3.1 (GND)
unnamed: C1.1, J2.T
unnamed: C4.1, R12.2, SW1.1
unnamed: D1.2 (A), R1.2
unnamed: D2.2 (A), D3.1 (K), R4.2, RV1.2, U1.2 (-)
unnamed: D2.1 (K), R6.2, R7.1
unnamed: D3.2 (A), R8.2, R9.1
unnamed: D4.2 (A), R10.2, U2.6
unnamed: D4.1 (K), Q1.3 (C)
unnamed: J3.T, U2.1
unnamed: Q1.2 (B), R11.1
unnamed: R5.1, RV1.1
unnamed: R5.2, R7.2, R8.1, U1.1, U2.2
unnamed: C2.1, R2.2, R3.1, U1.3 (+)
unnamed: C1.2, R4.1, U1.5 (+)
unnamed: U1.6 (-), U1.7, U2.8
unnamed: C7.1, U3.5 (CONT)
unnamed: R11.2, R12.1, U3.3 (OUT)
unnamed: R13.2, R14.1, SW1.2, U3.2 (TRIG), U3.6 (THRES)

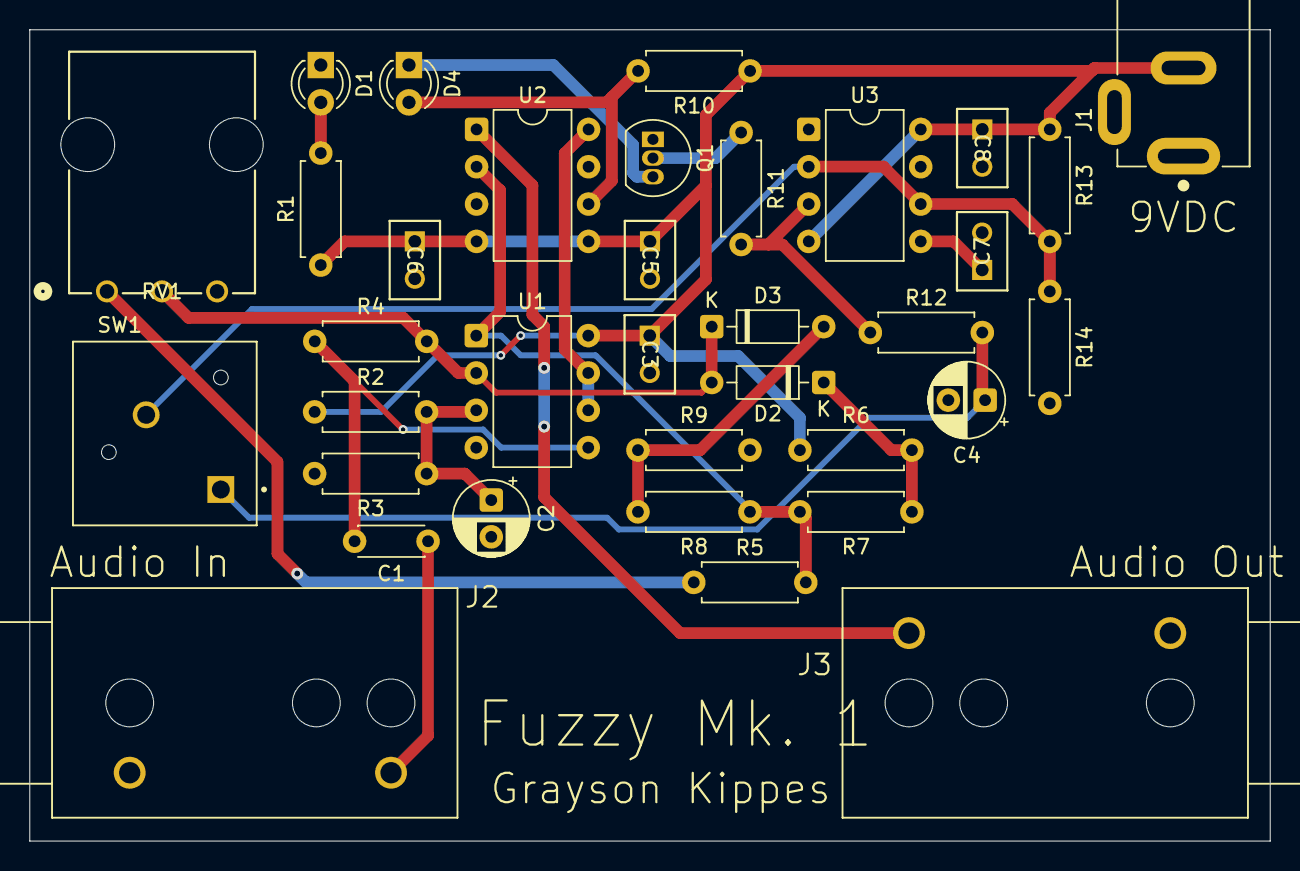
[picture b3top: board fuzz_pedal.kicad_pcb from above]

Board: 2 copper layers, 84.4 x 55.2 mm, 35 parts (0 on the bottom side), 20 nets.
